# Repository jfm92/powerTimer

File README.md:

# Power Timer

## Project Description

The Power Timer is an ultra-low power module that allows you to control the output power by software. It is mainly based on a Real-Time Clock (RTC) and an RS circuit. Thanks to the RTC, you can control the exact wake-up date or the periodicity. It also allows for external interruptions, which gives you the benefits of ultra-low power consumption while being able to connect other types of sensors. The module is based on the RV3028-C7 chip. It is also compatible with Arduino, thanks to its custom library.

The sleep current of the module is around 50nA at 3.3V, making it ideal for battery-powered applications.

## Consumption comparison:

Demo with software **sleep modes**:

Same demo **with powerTimer**:

### 734.000 times less idle consumption!

## How it works

The module is designed to be a versatile power control unit for your projects. It can be used as a simple timer to power on a device at a specific time or periodically, or it can be used as a power management unit that can be woken up by external events.

The PCB is divided into two parts:

*   **Input:** The input voltage (VINput) can be from 1.1V to 5.5V. This wide input range makes it compatible with a variety of power sources, from a single-cell Li-Po battery to a 5V power supply.

*   **Output:**
    *   **I2C:** The I2C pins (SDA and SCL) are used to program the RV3028-C7 RTC. You can set the time, date, and alarms using any microcontroller with I2C capabilities.
    *   **VOutput:** This pin will provide the same voltage as the input. When the module is in the "ON" state, the VOutput pin is connected to the VINput pin, providing power to your external device.
    *   **PWR_OFF:** This input allows you to externally cut off the power of the module. By pulling this pin high, you can force the module into the "OFF" state, even if the RTC alarm is active.
    *   **EXT_INT:** This input allows you to wake up the module externally using another sensor. This is useful for applications where you want to wake up the main device based on an external event, such as a button press or a sensor reading.
    *   **On-board button:** A push button is available on the board for manual wake-up. This allows you to turn on the module without relying on the RTC alarm or an external interrupt.

The logic levels of the I2C bus and the external interrupt input depend on the selected input voltage.

## Schematic

## PCB Layout

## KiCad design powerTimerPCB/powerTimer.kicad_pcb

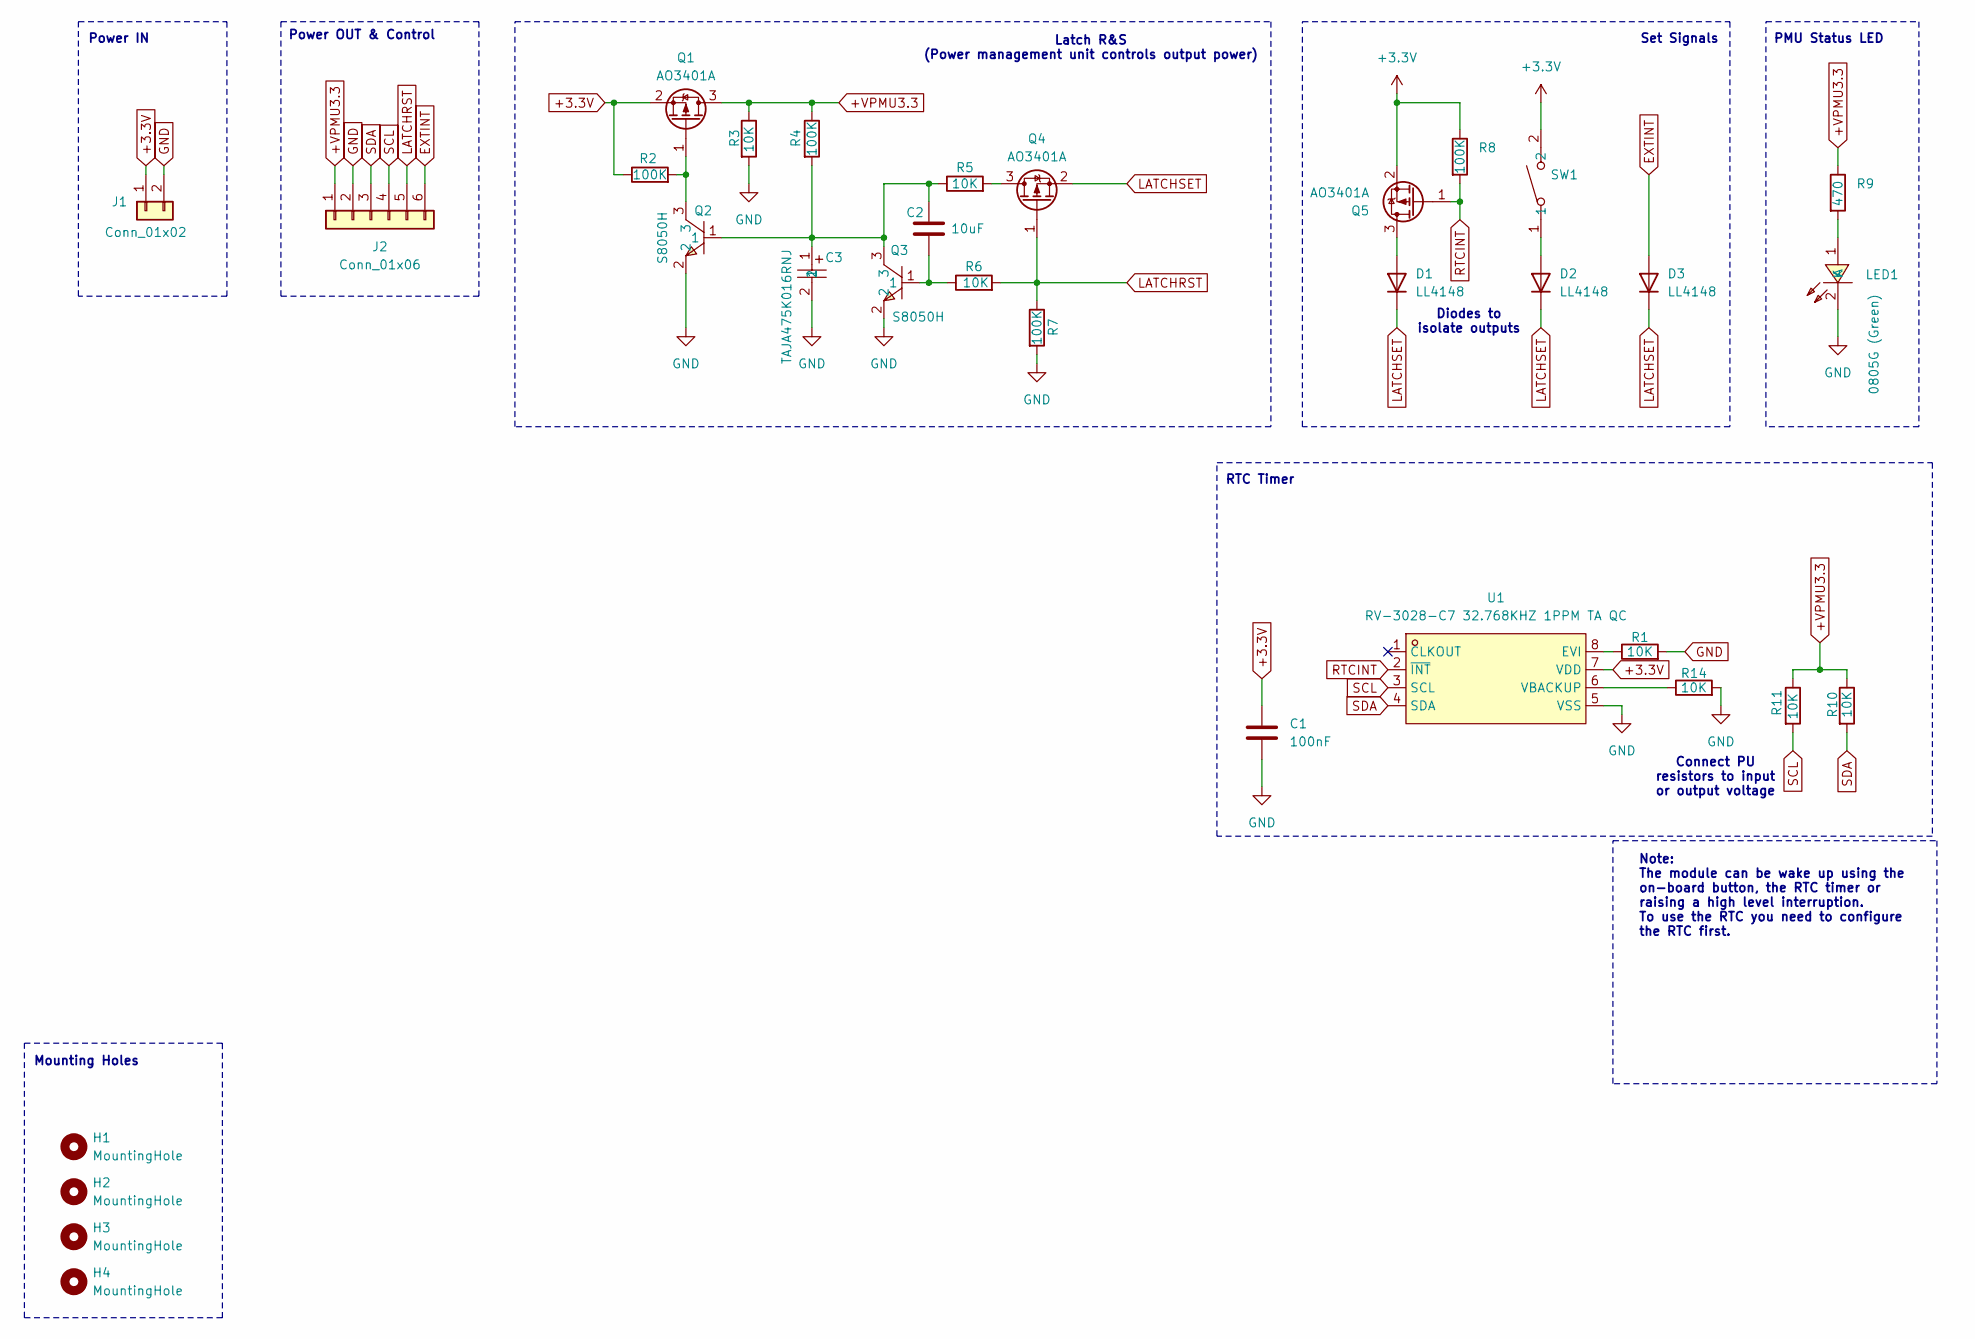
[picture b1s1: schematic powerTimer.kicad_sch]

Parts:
C1: 100nF; C_0603_1608Metric_Pad1.08x0.95mm_HandSolder
C2: 10uF; C_0603_1608Metric_Pad1.08x0.95mm_HandSolder
C3: TAJA475K016RNJ; CASE-A_3216; LCSC Part C7187
D1, D2, D3: LL4148; D_MiniMELF
H1, H2, H3, H4: MountingHole; MountingHole_2.2mm_M2_ISO7380
J1: Conn_01x02; PinHeader_1x02_P2.54mm_Vertical
J2: Conn_01x06; PinHeader_1x06_P2.54mm_Vertical
LED1: 0805G (Green); LED0805-R-RD; LCSC Part C2297
Q1, Q4, Q5: AO3401A; SOT-23
Q2, Q3: S8050H; SOT-23-3_L2.9-W1.6-P1.90-LS2.8-BR; LCSC Part C111272
R1, R3, R5, R6, R10, R11, R14: 10K; R_0603_1608Metric_Pad0.98x0.95mm_HandSolder
R2, R4, R7, R8: 100K; R_0603_1608Metric_Pad0.98x0.95mm_HandSolder
R9: 470; R_0603_1608Metric_Pad0.98x0.95mm_HandSolder
SW1: TS-1185EC-C-D-B; SW-SMD_4P-L3.7-W3.0-P1.50-LS4.7; LCSC Part C318893
U1: RV-3028-C7 32.768KHZ 1PPM TA QC; OSC-SMD_8P-L3.2-W1.5-P0.90-BL; LCSC Part C3019759

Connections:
+3.3V: C1.1, J1.1, Q1.2 (S), Q5.2 (S), R2.1, R8.1, SW1.2, U1.7 (VDD)
+VPMU3.3: J2.1, Q1.3 (D), R3.1, R4.1, R9.1, R10.1, R11.1
EXTINT: D3.2 (A), J2.6
GND: C1.2, C3.2, J1.2, J2.2, LED1.2 (K), Q2.2, Q3.2, R1.2, R3.2, R7.2, R14.2, U1.5 (VSS)
LATCHRST: J2.5, Q4.1 (G), R6.2, R7.1
LATCHSET: D1.1 (K), D2.1 (K), D3.1 (K), Q4.2 (S)
unnamed: C2.1, C3.1, Q2.1, Q3.3, R4.2, R5.1
unnamed: C2.2, Q3.1, R6.1
unnamed: D1.2 (A), Q5.3 (D)
unnamed: D2.2 (A), SW1.1
unnamed: LED1.1 (A), R9.2
unnamed: Q1.1 (G), Q2.3, R2.2
unnamed: Q4.3 (D), R5.2
unnamed: R1.1, U1.8 (EVI)
unnamed: R14.1, U1.6 (VBACKUP)
RTCINT: Q5.1 (G), R8.2, U1.2 (~INT)
SCL: J2.4, R11.2, U1.3 (SCL)
SDA: J2.3, R10.2, U1.4 (SDA)

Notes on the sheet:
RTC Timer
Latch R&S (Power management unit controls output power)
Note: The module can be wake up using the on-board button, the RTC timer or raising a high level interruption. To use the RTC you need to configure the RTC first.
Power OUT & Control
Set Signals
PMU Status LED
Power IN
Mounting Holes
Diodes to isolate outputs
Connect PU resistors to input or output voltage

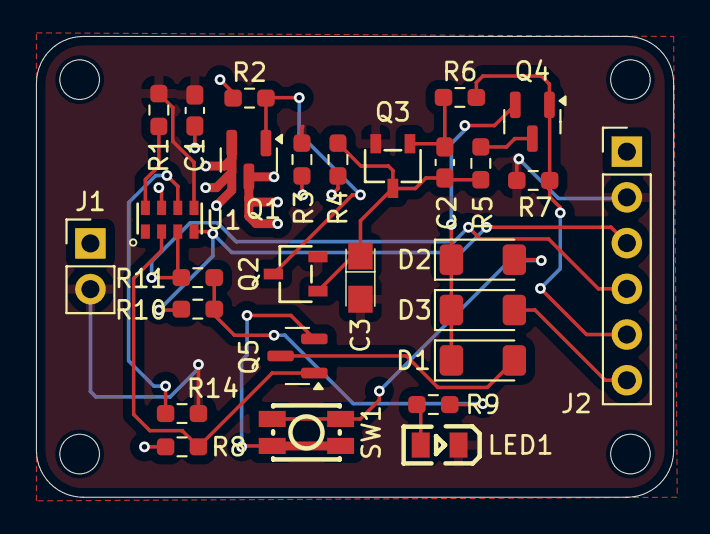
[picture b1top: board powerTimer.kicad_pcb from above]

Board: 2 copper layers, 35.4 x 25.6 mm, 32 parts (0 on the bottom side), 18 nets.

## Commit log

2025-06-28 Adding PCB design
2025-07-23 Moving lib to specific folder
2025-07-23 Minor change on MOSFET Q5 polarity
2025-09-13 Adding driver to the main repo
2025-11-07 Adding project readme
2025-11-07 Updating submodule version
2026-04-10 Adding powerProfiler images
2026-04-10 Updating README file
2026-04-11 Adding video demo
